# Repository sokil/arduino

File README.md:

# Arduino

Usefull snippets

## Troubleshooting:

### Error uploading sketch

```
ser_open(): can't open device "/dev/ttyACM0": Permission denied
```

Add rights to `tty` device:

```
sudo usermod -a -G dialout <username>
sudo chmod a+rw /dev/ttyACM0
```

## Avrdude

Update usbavr:
```
avrdude -c avrisp -P /dev/ttyACM0 -b 19200 -U flash:w:usbasp.atmega8.2011-05-28.hex:i -p m8
```

Flash app:
```
avrdude -c usbasp -U flash:w:firmware.hex:i -p m328p -b 9600

avrdude warning: cannot query manufacturer for device: error sending control message: Protocol error
avrdude warning: cannot query product for device: error sending control message: Protocol error
avrdude error: cannot find USB device with vid=0x16c0 pid=0x5dc vendor='www.fischl.de' product='USBasp'
avrdude error: unable to open programmer usbasp on port usb
```

```
$ lsusb
Bus 003 Device 021: ID 16c0:05dc Van Ooijen Technische Informatica shared ID for use with libusb
```

```
sudo chmod 666 /dev/bus/usb/003/009
```

```
cat /etc/udev/rules.d/99-USBasp.rules 
# USBasp - USB programmer for Atmel AVR controllers
# Copy this file to /etc/udev/rules.d so

SUBSYSTEM=="usb", ENV{DEVTYPE}=="usb_device", ATTRS{idVendor}=="16c0", ATTRS{idProduct}=="05dc", MODE="0666"
```

```
avrdude -c usbasp -U flash:w:firmware.hex:i -p m328p -b 9600 -P USB
```

```
$ tail -f /var/log/syslog
2024-03-31T01:14:27.068591+02:00 notebook kernel: [ 1296.030108] usb 3-4: USB disconnect, device number 10
2024-03-31T01:14:29.347815+02:00 notebook wpa_supplicant[870]: wlp0s20f3: WNM: Preferred List Available
2024-03-31T01:14:29.976557+02:00 notebook kernel: [ 1298.937165] usb 3-4: new low-speed USB device number 11 using xhci_hcd
2024-03-31T01:14:30.128593+02:00 notebook kernel: [ 1299.092344] usb 3-4: New USB device found, idVendor=16c0, idProduct=05dc, bcdDevice= 1.04
2024-03-31T01:14:30.128650+02:00 notebook kernel: [ 1299.092373] usb 3-4: New USB device strings: Mfr=1, Product=2, SerialNumber=0
2024-03-31T01:14:30.128652+02:00 notebook kernel: [ 1299.092378] usb 3-4: Product: USBasp
2024-03-31T01:14:30.128655+02:00 notebook kernel: [ 1299.092383] usb 3-4: Manufacturer: www.fischl.de
2024-03-31T01:14:30.136526+02:00 notebook mtp-probe: checking bus 3, device 11: "/sys/devices/pci0000:00/0000:00:14.0/usb3/3-4"
2024-03-31T01:14:30.136618+02:00 notebook mtp-probe: bus: 3, device: 11 was not an MTP device
2024-03-31T01:14:30.149249+02:00 notebook mtp-probe: checking bus 3, device 11: "/sys/devices/pci0000:00/0000:00:14.0/usb3/3-4"
2024-03-31T01:14:30.149310+02:00 notebook mtp-probe: bus: 3, device: 11 was not an MTP device
2024-03-31T01:14:34.362770+02:00 notebook wpa_supplicant[870]: wlp0s20f3: WNM: Preferred List Available

```

# esp8266

## Firmware

### Official firmware

* AT firmware: https://www.espressif.com/en/support/download/at
* Datasheet: https://www.espressif.com/sites/default/files/2a-esp8266-sdk_getting_started_guide_en_0.pdf

### NodeMCU

https://github.com/nodemcu/nodemcu-firmware

## Terminal

```
minicom -D /dev/ttyUSB0
Port: /dev/ttyUSB0
Baud Rate (Data Rate): 115200
Data Bits: 8
Parity: none
Stop bits: 1
Flow control: none
```

## AT commands

## Flasher

Initial boot address is 0x00000.

### ESPTool

https://github.com/espressif/esptool

```
sokil@hp:~$ sudo esptool.py -p /dev/ttyUSB0 flash_id
esptool.py v2.6
Serial port /dev/ttyUSB0
Connecting....
Detecting chip type... ESP8266
Chip is ESP8266EX
Features: WiFi
MAC: 18:fe:34:d3:1f:b5
Uploading stub...
Running stub...
Stub running...
Manufacturer: e0
Device: 4014
Detected flash size: 1MB
Hard resetting via RTS pin...
```

Download latest firmware at: https://www.espressif.com/en/support/download/at?keys=&field_type_tid%5B%5D=14

Or extract local AT_V1.1_on_ESP8266_NONOS_SDK_V1.5.4.zip.

Flash it:

```
$ sudo esptool.py -p /dev/ttyUSB0 write_flash 0x00000 boot_v1.5.bin  0x01000 512+512/user1.1024.new.2.bin  0xfc000  esp_init_data_default.bin  0x7e000  blank.bin 0xfe000 blank.bin
esptool.py v2.6
Serial port /dev/ttyUSB0
Connecting....
Detecting chip type... ESP8266
Chip is ESP8266EX
Features: WiFi
MAC: 18:fe:34:d3:1f:b5
Uploading stub...
Running stub...
Stub running...
Configuring flash size...
Auto-detected Flash size: 1MB
Flash params set to 0x0020
Compressed 3232 bytes to 2336...
Wrote 3232 bytes (2336 compressed) at 0x00000000 in 0.2 seconds (effective 122.2 kbit/s)...
Hash of data verified.
Compressed 399204 bytes to 286943...
Wrote 399204 bytes (286943 compressed) at 0x00001000 in 25.6 seconds (effective 125.0 kbit/s)...
Hash of data verified.
Compressed 128 bytes to 77...
Wrote 128 bytes (77 compressed) at 0x000fc000 in 0.0 seconds (effective 93.5 kbit/s)...
Hash of data verified.
Compressed 4096 bytes to 26...
Wrote 4096 bytes (26 compressed) at 0x0007e000 in 0.0 seconds (effective 5224.4 kbit/s)...
Hash of data verified.
Compressed 4096 bytes to 26...
Wrote 4096 bytes (26 compressed) at 0x000fe000 in 0.0 seconds (effective 5422.5 kbit/s)...
Hash of data verified.

Leaving...
Hard resetting via RTS pin...

```

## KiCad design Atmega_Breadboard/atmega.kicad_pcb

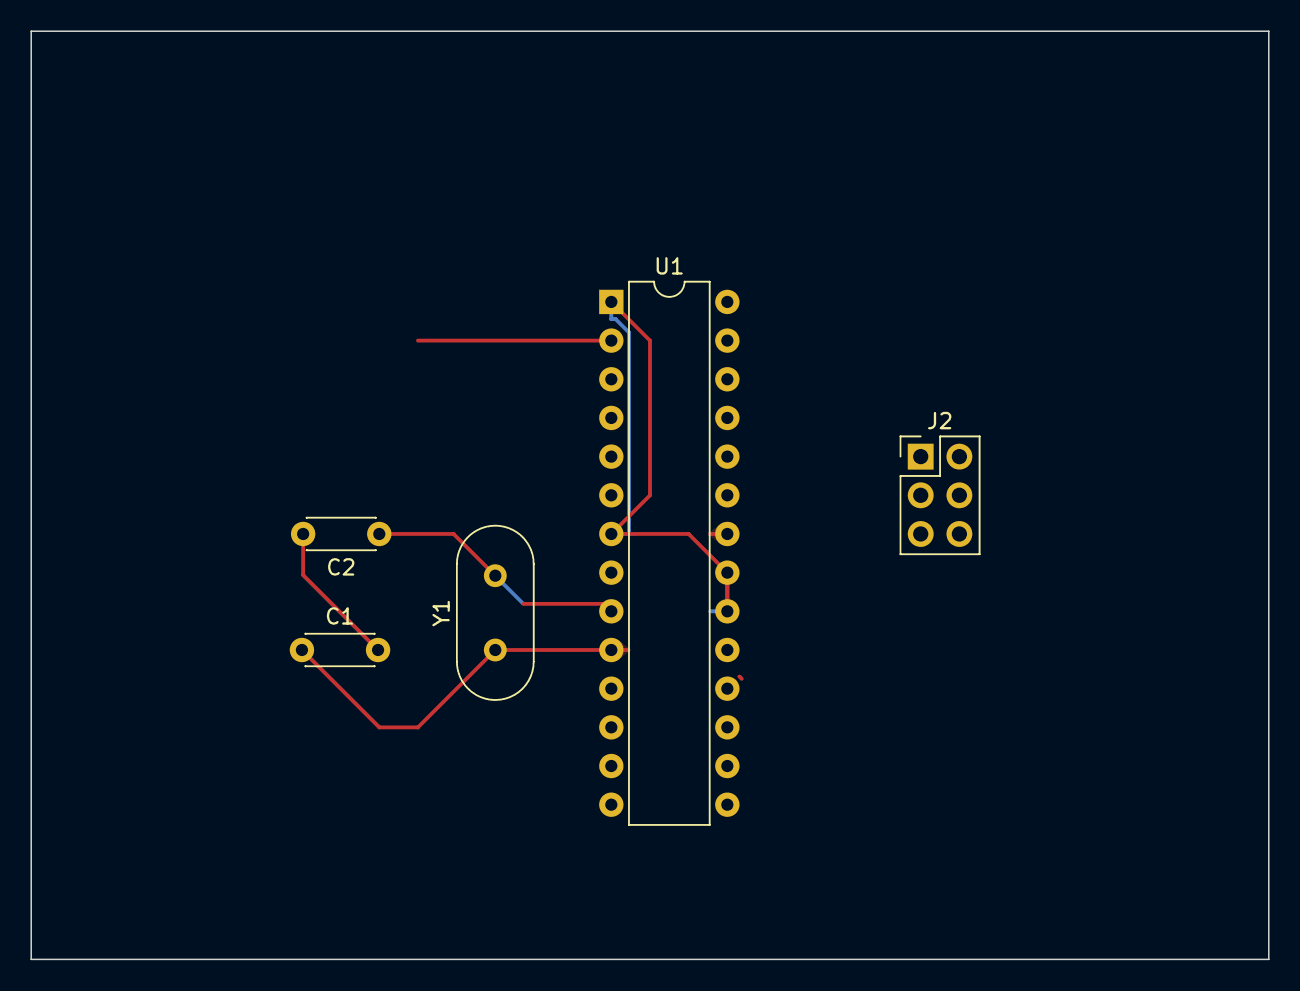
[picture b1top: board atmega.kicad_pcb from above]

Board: 2 copper layers, 81.3 x 61.0 mm, 5 parts (0 on the bottom side), 4 nets.

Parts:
C1, C2: 22pf; C_Disc_D4.3mm_W1.9mm_P5.00mm
J2: Conn_02x03_Row_Letter_First; PinHeader_2x03_P2.54mm_Vertical
U1: ATmega328P-P; DIP-28_W7.62mm
Y1: Crystal; Crystal_HC49-4H_Vertical

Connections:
+5V: U1.1 (~RESET/PC6), U1.7 (VCC), U1.20 (AVCC), U1.21 (AREF)
GND: C1.2, C2.2, U1.8 (GND), U1.22 (GND)
unnamed: C2.1, U1.9 (XTAL1/PB6), Y1.2
unnamed: C1.1, U1.10 (XTAL2/PB7), Y1.1

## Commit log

2018-01-07 check usb serial ttl converter
2018-01-07 rename
2018-01-07 create projects
2024-03-30 oled by i2c, shift register
2024-04-04 new projects
2024-04-10 firmware
2024-07-07 adapt for nodemcu
2024-10-14 baro
2025-01-10 spi sniff
2026-01-02 clap lantern
2026-01-21 freertos
2026-01-21 echo
2026-01-22 esp32 cam
2026-01-29 rgb blink neopixel
